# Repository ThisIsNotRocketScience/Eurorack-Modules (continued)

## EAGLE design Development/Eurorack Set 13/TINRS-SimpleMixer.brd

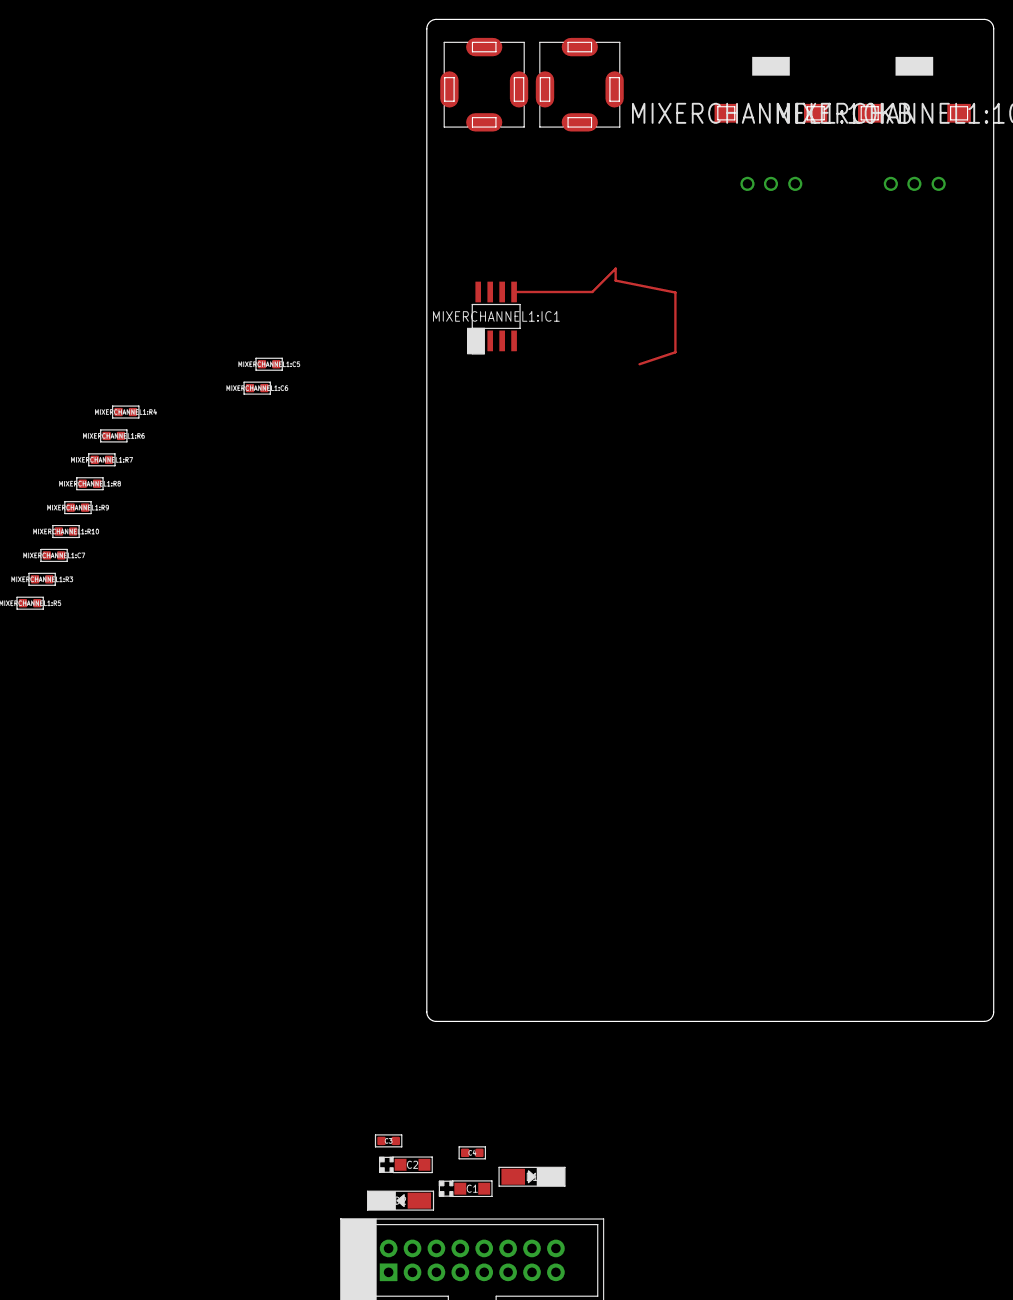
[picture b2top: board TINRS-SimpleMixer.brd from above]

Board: 2 copper layers, 60.2 x 106.5 mm, 24 parts (0 on the bottom side), 16 nets.

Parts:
C1, C2: CASE-A_3216
C3, C4: 100n; C0603
D1, D2: DO-214AC
J1: POWERSHROUDED; POWER_16_SHROUDED
MIXERCHANNEL1:10KA, MIXERCHANNEL1:10KB: ALPS_POT_SQUAREHOLES
MIXERCHANNEL1:C5, MIXERCHANNEL1:C6: 100n; C0603
MIXERCHANNEL1:C7: 100p; C0603
MIXERCHANNEL1:IC1: NE5532D; SO08
MIXERCHANNEL1:J2, MIXERCHANNEL1:J3: JACK; 3.5MM-JACK-SWITCH-13MM-NOHOLES
MIXERCHANNEL1:R3, MIXERCHANNEL1:R5: 2.2k; R0603
MIXERCHANNEL1:R4, MIXERCHANNEL1:R6, MIXERCHANNEL1:R7, MIXERCHANNEL1:R8, MIXERCHANNEL1:R9: 4.7k; R0603
MIXERCHANNEL1:R10: 56; R0603
PCB1: EURORACK_PCB12HP; EURORACK12HPPCB

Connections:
12V: C1.+, C4.1, D1.2, MIXERCHANNEL1:C6.1, MIXERCHANNEL1:IC1.8
-12V: C2.-, C3.2, D2.1, MIXERCHANNEL1:C5.2, MIXERCHANNEL1:IC1.4
GND: C1.-, C2.+, C3.1, C4.2, J1.3, J1.4, J1.5, J1.6, J1.7, J1.8, MIXERCHANNEL1:10KA.P$1, MIXERCHANNEL1:10KB.P$2, MIXERCHANNEL1:C5.1, MIXERCHANNEL1:C6.2, MIXERCHANNEL1:IC1.3, MIXERCHANNEL1:IC1.5, MIXERCHANNEL1:J2.RING_B@1, MIXERCHANNEL1:J2.RING_T@3, MIXERCHANNEL1:J2.SWITCH_B@1, MIXERCHANNEL1:J2.SWITCH_T@3, MIXERCHANNEL1:J3.RING_B@1, MIXERCHANNEL1:J3.RING_T@3, MIXERCHANNEL1:J3.SWITCH_B@1, MIXERCHANNEL1:J3.SWITCH_T@3
MIXERCHANNEL1:N$1: MIXERCHANNEL1:C7.2, MIXERCHANNEL1:IC1.6, MIXERCHANNEL1:R6.2, MIXERCHANNEL1:R7.1
MIXERCHANNEL1:N$2: MIXERCHANNEL1:IC1.2, MIXERCHANNEL1:R4.2, MIXERCHANNEL1:R8.2, MIXERCHANNEL1:R9.1
MIXERCHANNEL1:N$3: MIXERCHANNEL1:10KA.P$2, MIXERCHANNEL1:R6.1
MIXERCHANNEL1:N$4: MIXERCHANNEL1:10KA.P$3, MIXERCHANNEL1:IC1.1, MIXERCHANNEL1:R9.2
MIXERCHANNEL1:N$5: MIXERCHANNEL1:R3.1, MIXERCHANNEL1:R5.1, MIXERCHANNEL1:R7.2, MIXERCHANNEL1:R10.2
MIXERCHANNEL1:N$10: MIXERCHANNEL1:J2.TIP_B@1, MIXERCHANNEL1:J2.TIP_T@3, MIXERCHANNEL1:R4.1
MIXERCHANNEL1:N$11: MIXERCHANNEL1:J3.TIP_B@1, MIXERCHANNEL1:J3.TIP_T@3, MIXERCHANNEL1:R8.1
MIXERCHANNEL1:N$12: MIXERCHANNEL1:IC1.7, MIXERCHANNEL1:R10.1
MIXERCHANNEL1:N$13: MIXERCHANNEL1:C7.1, MIXERCHANNEL1:IC1.7
MIXERCHANNEL1:OUT_L: MIXERCHANNEL1:10KB.P$3, MIXERCHANNEL1:R5.2
MIXERCHANNEL1:OUT_R: MIXERCHANNEL1:10KB.P$1, MIXERCHANNEL1:R3.2
unnamed: D1.1, J1.9, J1.10
unnamed: D2.2, J1.1, J1.2

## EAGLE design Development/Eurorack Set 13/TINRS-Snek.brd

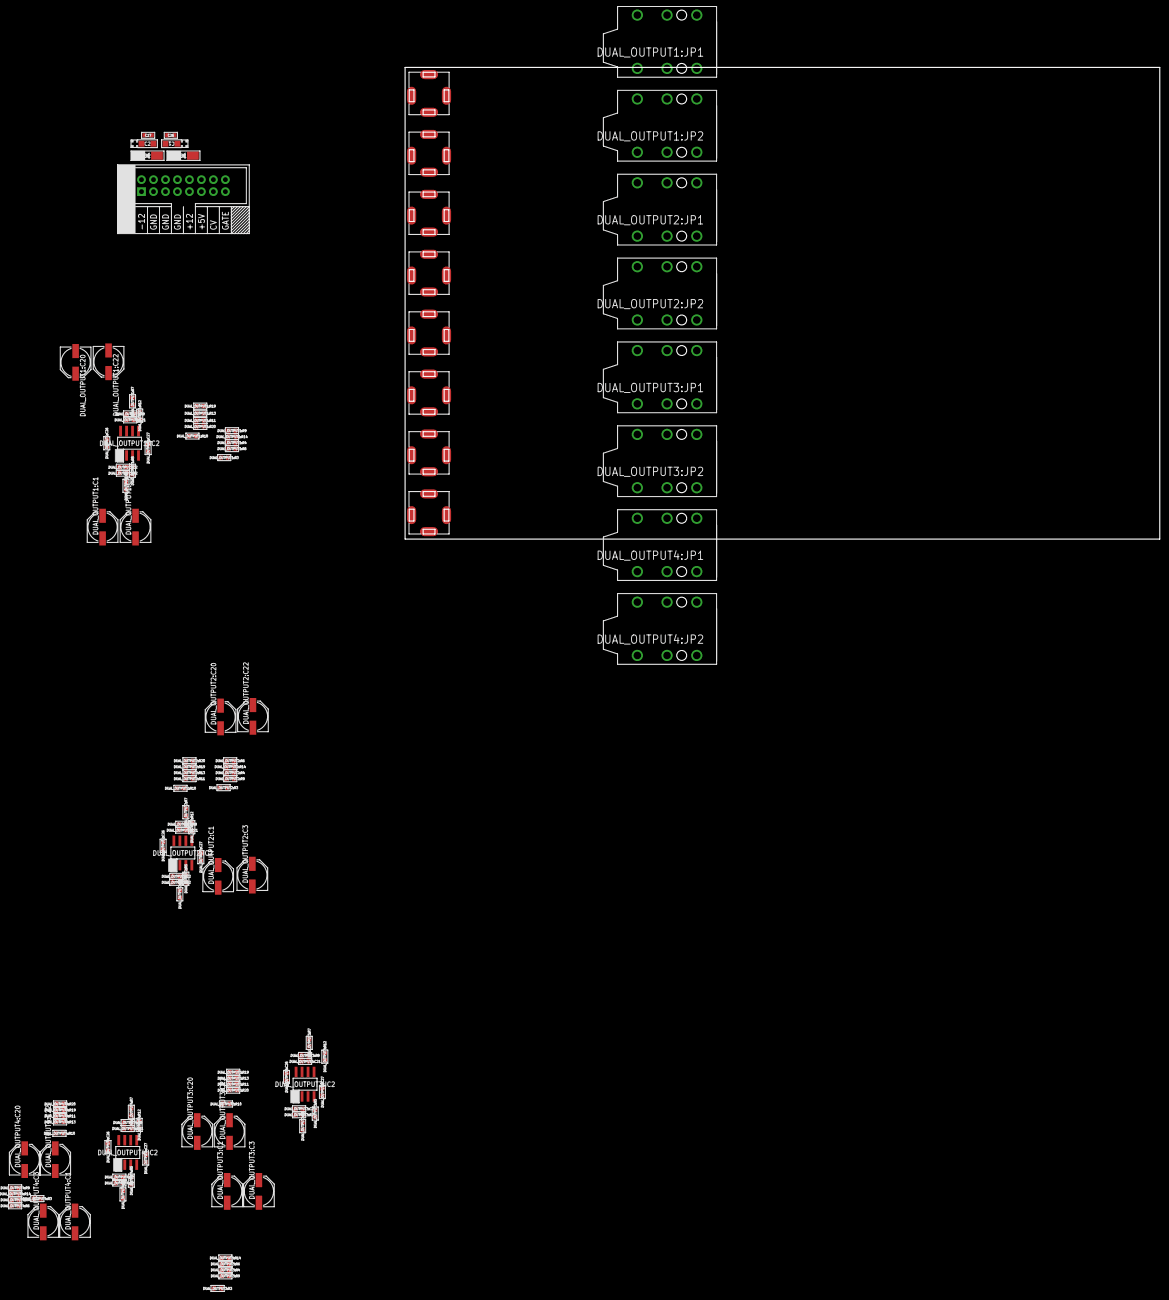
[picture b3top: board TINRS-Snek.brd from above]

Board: 2 copper layers, 160.0 x 100.0 mm, 123 parts (0 on the bottom side), 64 nets, no tracks yet.

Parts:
C1, C2: 10u; CASE-A_3216
C26, C27: 100n; C0603
D1, D2: DO-214AC
DUAL_OUTPUT1:C1, DUAL_OUTPUT1:C3, DUAL_OUTPUT1:C20, DUAL_OUTPUT1:C22, DUAL_OUTPUT2:C1, DUAL_OUTPUT2:C3, DUAL_OUTPUT2:C20, DUAL_OUTPUT2:C22, DUAL_OUTPUT3:C1, DUAL_OUTPUT3:C3, DUAL_OUTPUT3:C20, DUAL_OUTPUT3:C22, DUAL_OUTPUT4:C1, DUAL_OUTPUT4:C3, DUAL_OUTPUT4:C20, DUAL_OUTPUT4:C22: 100u; PANASONIC_D
DUAL_OUTPUT1:C2, DUAL_OUTPUT1:C21, DUAL_OUTPUT2:C2, DUAL_OUTPUT2:C21, DUAL_OUTPUT3:C2, DUAL_OUTPUT3:C21, DUAL_OUTPUT4:C2, DUAL_OUTPUT4:C21: 22p; C0603
DUAL_OUTPUT1:C26, DUAL_OUTPUT1:C27, DUAL_OUTPUT2:C26, DUAL_OUTPUT2:C27, DUAL_OUTPUT3:C26, DUAL_OUTPUT3:C27, DUAL_OUTPUT4:C26, DUAL_OUTPUT4:C27: 100n; C0603
DUAL_OUTPUT1:IC2, DUAL_OUTPUT2:IC2, DUAL_OUTPUT3:IC2, DUAL_OUTPUT4:IC2: NE5532D; SO08
DUAL_OUTPUT1:J1, DUAL_OUTPUT1:J2, DUAL_OUTPUT2:J1, DUAL_OUTPUT2:J2, DUAL_OUTPUT3:J1, DUAL_OUTPUT3:J2, DUAL_OUTPUT4:J1, DUAL_OUTPUT4:J2: JACK; 3.5MM-JACK-SWITCH-13MM-NOHOLES
DUAL_OUTPUT1:JP1, DUAL_OUTPUT1:JP2, DUAL_OUTPUT2:JP1, DUAL_OUTPUT2:JP2, DUAL_OUTPUT3:JP1, DUAL_OUTPUT3:JP2, DUAL_OUTPUT4:JP1, DUAL_OUTPUT4:JP2: AUDIO-JACK-.25-INCH-HORIZ-PTH
DUAL_OUTPUT1:R1, DUAL_OUTPUT1:R2, DUAL_OUTPUT1:R7, DUAL_OUTPUT1:R8, DUAL_OUTPUT2:R1, DUAL_OUTPUT2:R2, DUAL_OUTPUT2:R7, DUAL_OUTPUT2:R8, DUAL_OUTPUT3:R1, DUAL_OUTPUT3:R2, DUAL_OUTPUT3:R7, DUAL_OUTPUT3:R8, DUAL_OUTPUT4:R1, DUAL_OUTPUT4:R2, DUAL_OUTPUT4:R7, DUAL_OUTPUT4:R8: 4.7k; R0603
DUAL_OUTPUT1:R3, DUAL_OUTPUT1:R10, DUAL_OUTPUT2:R3, DUAL_OUTPUT2:R10, DUAL_OUTPUT3:R3, DUAL_OUTPUT3:R10, DUAL_OUTPUT4:R3, DUAL_OUTPUT4:R10: 56k; R0603
DUAL_OUTPUT1:R4, DUAL_OUTPUT1:R6, DUAL_OUTPUT1:R9, DUAL_OUTPUT1:R11, DUAL_OUTPUT1:R13, DUAL_OUTPUT1:R14, DUAL_OUTPUT1:R19, DUAL_OUTPUT1:R20, DUAL_OUTPUT2:R4, DUAL_OUTPUT2:R6, DUAL_OUTPUT2:R9, DUAL_OUTPUT2:R11, DUAL_OUTPUT2:R13, DUAL_OUTPUT2:R14, DUAL_OUTPUT2:R19, DUAL_OUTPUT2:R20, DUAL_OUTPUT3:R4, DUAL_OUTPUT3:R6, DUAL_OUTPUT3:R9, DUAL_OUTPUT3:R11, DUAL_OUTPUT3:R13, DUAL_OUTPUT3:R14, DUAL_OUTPUT3:R19, DUAL_OUTPUT3:R20, DUAL_OUTPUT4:R4, DUAL_OUTPUT4:R6, DUAL_OUTPUT4:R9, DUAL_OUTPUT4:R11, DUAL_OUTPUT4:R13, DUAL_OUTPUT4:R14, DUAL_OUTPUT4:R19, DUAL_OUTPUT4:R20: 220; R0603
DUAL_OUTPUT1:R5, DUAL_OUTPUT1:R12, DUAL_OUTPUT2:R5, DUAL_OUTPUT2:R12, DUAL_OUTPUT3:R5, DUAL_OUTPUT3:R12, DUAL_OUTPUT4:R5, DUAL_OUTPUT4:R12: 27; R0603
J5: POWERSHROUDED; POWER_16_SHROUDED

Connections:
5V: J5.11, J5.12
12V: C1.+, C26.2, D1.2, DUAL_OUTPUT1:C26.2, DUAL_OUTPUT1:IC2.8, DUAL_OUTPUT2:C26.2, DUAL_OUTPUT2:IC2.8, DUAL_OUTPUT3:C26.2, DUAL_OUTPUT3:IC2.8, DUAL_OUTPUT4:C26.2, DUAL_OUTPUT4:IC2.8
-12V: C2.-, C27.1, D2.1, DUAL_OUTPUT1:C27.1, DUAL_OUTPUT1:IC2.4, DUAL_OUTPUT2:C27.1, DUAL_OUTPUT2:IC2.4, DUAL_OUTPUT3:C27.1, DUAL_OUTPUT3:IC2.4, DUAL_OUTPUT4:C27.1, DUAL_OUTPUT4:IC2.4
CV1: J5.13, J5.14
DUAL_OUTPUT1:N$1: DUAL_OUTPUT1:C21.1, DUAL_OUTPUT1:IC2.6, DUAL_OUTPUT1:R7.1, DUAL_OUTPUT1:R8.2
DUAL_OUTPUT1:N$2: DUAL_OUTPUT1:C20.+, DUAL_OUTPUT1:C21.2, DUAL_OUTPUT1:IC2.7, DUAL_OUTPUT1:R8.1
DUAL_OUTPUT1:N$3: DUAL_OUTPUT1:C22.+, DUAL_OUTPUT1:R10.1, DUAL_OUTPUT1:R11.1, DUAL_OUTPUT1:R13.1, DUAL_OUTPUT1:R19.1, DUAL_OUTPUT1:R20.1
DUAL_OUTPUT1:N$4: DUAL_OUTPUT1:IC2.5, DUAL_OUTPUT1:R12.1
DUAL_OUTPUT1:N$5: DUAL_OUTPUT1:C2.1, DUAL_OUTPUT1:IC2.2, DUAL_OUTPUT1:R1.1, DUAL_OUTPUT1:R2.2
DUAL_OUTPUT1:N$6: DUAL_OUTPUT1:C1.+, DUAL_OUTPUT1:C2.2, DUAL_OUTPUT1:IC2.1, DUAL_OUTPUT1:R2.1
DUAL_OUTPUT1:N$7: DUAL_OUTPUT1:C3.+, DUAL_OUTPUT1:R3.1, DUAL_OUTPUT1:R4.1, DUAL_OUTPUT1:R6.1, DUAL_OUTPUT1:R9.1, DUAL_OUTPUT1:R14.1
DUAL_OUTPUT1:N$8: DUAL_OUTPUT1:IC2.3, DUAL_OUTPUT1:R5.1
DUAL_OUTPUT1:N$11: DUAL_OUTPUT1:C20.-, DUAL_OUTPUT1:C22.-
DUAL_OUTPUT1:N$12: DUAL_OUTPUT1:C1.-, DUAL_OUTPUT1:C3.-
DUAL_OUTPUT1:OUT1: DUAL_OUTPUT1:J1.TIP_B@1, DUAL_OUTPUT1:J1.TIP_T@3, DUAL_OUTPUT1:R1.2
DUAL_OUTPUT1:OUT2: DUAL_OUTPUT1:J2.TIP_B@1, DUAL_OUTPUT1:J2.TIP_T@3, DUAL_OUTPUT1:R7.2
DUAL_OUTPUT1:TIP1: DUAL_OUTPUT1:JP1.P$6, DUAL_OUTPUT1:R4.2, DUAL_OUTPUT1:R6.2, DUAL_OUTPUT1:R9.2, DUAL_OUTPUT1:R14.2
DUAL_OUTPUT1:TIP2: DUAL_OUTPUT1:JP2.P$6, DUAL_OUTPUT1:R11.2, DUAL_OUTPUT1:R13.2, DUAL_OUTPUT1:R19.2, DUAL_OUTPUT1:R20.2
DUAL_OUTPUT2:N$1: DUAL_OUTPUT2:C21.1, DUAL_OUTPUT2:IC2.6, DUAL_OUTPUT2:R7.1, DUAL_OUTPUT2:R8.2
DUAL_OUTPUT2:N$2: DUAL_OUTPUT2:C20.+, DUAL_OUTPUT2:C21.2, DUAL_OUTPUT2:IC2.7, DUAL_OUTPUT2:R8.1
DUAL_OUTPUT2:N$3: DUAL_OUTPUT2:C22.+, DUAL_OUTPUT2:R10.1, DUAL_OUTPUT2:R11.1, DUAL_OUTPUT2:R13.1, DUAL_OUTPUT2:R19.1, DUAL_OUTPUT2:R20.1
DUAL_OUTPUT2:N$4: DUAL_OUTPUT2:IC2.5, DUAL_OUTPUT2:R12.1
DUAL_OUTPUT2:N$5: DUAL_OUTPUT2:C2.1, DUAL_OUTPUT2:IC2.2, DUAL_OUTPUT2:R1.1, DUAL_OUTPUT2:R2.2
DUAL_OUTPUT2:N$6: DUAL_OUTPUT2:C1.+, DUAL_OUTPUT2:C2.2, DUAL_OUTPUT2:IC2.1, DUAL_OUTPUT2:R2.1
DUAL_OUTPUT2:N$7: DUAL_OUTPUT2:C3.+, DUAL_OUTPUT2:R3.1, DUAL_OUTPUT2:R4.1, DUAL_OUTPUT2:R6.1, DUAL_OUTPUT2:R9.1, DUAL_OUTPUT2:R14.1
DUAL_OUTPUT2:N$8: DUAL_OUTPUT2:IC2.3, DUAL_OUTPUT2:R5.1
DUAL_OUTPUT2:N$11: DUAL_OUTPUT2:C20.-, DUAL_OUTPUT2:C22.-
DUAL_OUTPUT2:N$12: DUAL_OUTPUT2:C1.-, DUAL_OUTPUT2:C3.-
DUAL_OUTPUT2:OUT1: DUAL_OUTPUT2:J1.TIP_B@1, DUAL_OUTPUT2:J1.TIP_T@3, DUAL_OUTPUT2:R1.2
DUAL_OUTPUT2:OUT2: DUAL_OUTPUT2:J2.TIP_B@1, DUAL_OUTPUT2:J2.TIP_T@3, DUAL_OUTPUT2:R7.2
DUAL_OUTPUT2:TIP1: DUAL_OUTPUT2:JP1.P$6, DUAL_OUTPUT2:R4.2, DUAL_OUTPUT2:R6.2, DUAL_OUTPUT2:R9.2, DUAL_OUTPUT2:R14.2
DUAL_OUTPUT2:TIP2: DUAL_OUTPUT2:JP2.P$6, DUAL_OUTPUT2:R11.2, DUAL_OUTPUT2:R13.2, DUAL_OUTPUT2:R19.2, DUAL_OUTPUT2:R20.2
DUAL_OUTPUT3:N$1: DUAL_OUTPUT3:C21.1, DUAL_OUTPUT3:IC2.6, DUAL_OUTPUT3:R7.1, DUAL_OUTPUT3:R8.2
DUAL_OUTPUT3:N$2: DUAL_OUTPUT3:C20.+, DUAL_OUTPUT3:C21.2, DUAL_OUTPUT3:IC2.7, DUAL_OUTPUT3:R8.1
DUAL_OUTPUT3:N$3: DUAL_OUTPUT3:C22.+, DUAL_OUTPUT3:R10.1, DUAL_OUTPUT3:R11.1, DUAL_OUTPUT3:R13.1, DUAL_OUTPUT3:R19.1, DUAL_OUTPUT3:R20.1
DUAL_OUTPUT3:N$4: DUAL_OUTPUT3:IC2.5, DUAL_OUTPUT3:R12.1
DUAL_OUTPUT3:N$5: DUAL_OUTPUT3:C2.1, DUAL_OUTPUT3:IC2.2, DUAL_OUTPUT3:R1.1, DUAL_OUTPUT3:R2.2
DUAL_OUTPUT3:N$6: DUAL_OUTPUT3:C1.+, DUAL_OUTPUT3:C2.2, DUAL_OUTPUT3:IC2.1, DUAL_OUTPUT3:R2.1
DUAL_OUTPUT3:N$7: DUAL_OUTPUT3:C3.+, DUAL_OUTPUT3:R3.1, DUAL_OUTPUT3:R4.1, DUAL_OUTPUT3:R6.1, DUAL_OUTPUT3:R9.1, DUAL_OUTPUT3:R14.1
DUAL_OUTPUT3:N$8: DUAL_OUTPUT3:IC2.3, DUAL_OUTPUT3:R5.1
DUAL_OUTPUT3:N$11: DUAL_OUTPUT3:C20.-, DUAL_OUTPUT3:C22.-
DUAL_OUTPUT3:N$12: DUAL_OUTPUT3:C1.-, DUAL_OUTPUT3:C3.-
DUAL_OUTPUT3:OUT1: DUAL_OUTPUT3:J1.TIP_B@1, DUAL_OUTPUT3:J1.TIP_T@3, DUAL_OUTPUT3:R1.2
DUAL_OUTPUT3:OUT2: DUAL_OUTPUT3:J2.TIP_B@1, DUAL_OUTPUT3:J2.TIP_T@3, DUAL_OUTPUT3:R7.2
DUAL_OUTPUT3:TIP1: DUAL_OUTPUT3:JP1.P$6, DUAL_OUTPUT3:R4.2, DUAL_OUTPUT3:R6.2, DUAL_OUTPUT3:R9.2, DUAL_OUTPUT3:R14.2
DUAL_OUTPUT3:TIP2: DUAL_OUTPUT3:JP2.P$6, DUAL_OUTPUT3:R11.2, DUAL_OUTPUT3:R13.2, DUAL_OUTPUT3:R19.2, DUAL_OUTPUT3:R20.2
DUAL_OUTPUT4:N$1: DUAL_OUTPUT4:C21.1, DUAL_OUTPUT4:IC2.6, DUAL_OUTPUT4:R7.1, DUAL_OUTPUT4:R8.2
DUAL_OUTPUT4:N$2: DUAL_OUTPUT4:C20.+, DUAL_OUTPUT4:C21.2, DUAL_OUTPUT4:IC2.7, DUAL_OUTPUT4:R8.1
DUAL_OUTPUT4:N$3: DUAL_OUTPUT4:C22.+, DUAL_OUTPUT4:R10.1, DUAL_OUTPUT4:R11.1, DUAL_OUTPUT4:R13.1, DUAL_OUTPUT4:R19.1, DUAL_OUTPUT4:R20.1
DUAL_OUTPUT4:N$4: DUAL_OUTPUT4:IC2.5, DUAL_OUTPUT4:R12.1
DUAL_OUTPUT4:N$5: DUAL_OUTPUT4:C2.1, DUAL_OUTPUT4:IC2.2, DUAL_OUTPUT4:R1.1, DUAL_OUTPUT4:R2.2
DUAL_OUTPUT4:N$6: DUAL_OUTPUT4:C1.+, DUAL_OUTPUT4:C2.2, DUAL_OUTPUT4:IC2.1, DUAL_OUTPUT4:R2.1
DUAL_OUTPUT4:N$7: DUAL_OUTPUT4:C3.+, DUAL_OUTPUT4:R3.1, DUAL_OUTPUT4:R4.1, DUAL_OUTPUT4:R6.1, DUAL_OUTPUT4:R9.1, DUAL_OUTPUT4:R14.1
DUAL_OUTPUT4:N$8: DUAL_OUTPUT4:IC2.3, DUAL_OUTPUT4:R5.1
DUAL_OUTPUT4:N$11: DUAL_OUTPUT4:C20.-, DUAL_OUTPUT4:C22.-
DUAL_OUTPUT4:N$12: DUAL_OUTPUT4:C1.-, DUAL_OUTPUT4:C3.-
DUAL_OUTPUT4:OUT1: DUAL_OUTPUT4:J1.TIP_B@1, DUAL_OUTPUT4:J1.TIP_T@3, DUAL_OUTPUT4:R1.2
DUAL_OUTPUT4:OUT2: DUAL_OUTPUT4:J2.TIP_B@1, DUAL_OUTPUT4:J2.TIP_T@3, DUAL_OUTPUT4:R7.2
DUAL_OUTPUT4:TIP1: DUAL_OUTPUT4:JP1.P$6, DUAL_OUTPUT4:R4.2, DUAL_OUTPUT4:R6.2, DUAL_OUTPUT4:R9.2, DUAL_OUTPUT4:R14.2
DUAL_OUTPUT4:TIP2: DUAL_OUTPUT4:JP2.P$6, DUAL_OUTPUT4:R11.2, DUAL_OUTPUT4:R13.2, DUAL_OUTPUT4:R19.2, DUAL_OUTPUT4:R20.2
G1: J5.15, J5.16
GND: C1.-, C2.+, C26.1, DUAL_OUTPUT1:C26.1, DUAL_OUTPUT1:C27.2, DUAL_OUTPUT1:J1.RING_B@1, DUAL_OUTPUT1:J1.RING_T@3, DUAL_OUTPUT1:J1.SWITCH_B@1, DUAL_OUTPUT1:J1.SWITCH_T@3, DUAL_OUTPUT1:J2.RING_B@1, DUAL_OUTPUT1:J2.RING_T@3, DUAL_OUTPUT1:J2.SWITCH_B@1, DUAL_OUTPUT1:J2.SWITCH_T@3, DUAL_OUTPUT1:JP1.P$2, DUAL_OUTPUT1:JP1.P$3, DUAL_OUTPUT1:JP1.P$4, DUAL_OUTPUT1:JP2.P$2, DUAL_OUTPUT1:JP2.P$3, DUAL_OUTPUT1:JP2.P$4, DUAL_OUTPUT1:R3.2, DUAL_OUTPUT1:R5.2, DUAL_OUTPUT1:R10.2, DUAL_OUTPUT1:R12.2, DUAL_OUTPUT2:C26.1, DUAL_OUTPUT2:C27.2, DUAL_OUTPUT2:J1.RING_B@1, DUAL_OUTPUT2:J1.RING_T@3, DUAL_OUTPUT2:J1.SWITCH_B@1, DUAL_OUTPUT2:J1.SWITCH_T@3, DUAL_OUTPUT2:J2.RING_B@1, DUAL_OUTPUT2:J2.RING_T@3, DUAL_OUTPUT2:J2.SWITCH_B@1, DUAL_OUTPUT2:J2.SWITCH_T@3, DUAL_OUTPUT2:JP1.P$2, DUAL_OUTPUT2:JP1.P$3, DUAL_OUTPUT2:JP1.P$4, DUAL_OUTPUT2:JP2.P$2, DUAL_OUTPUT2:JP2.P$3, DUAL_OUTPUT2:JP2.P$4, DUAL_OUTPUT2:R3.2, DUAL_OUTPUT2:R5.2, DUAL_OUTPUT2:R10.2, DUAL_OUTPUT2:R12.2, DUAL_OUTPUT3:C26.1, DUAL_OUTPUT3:C27.2, DUAL_OUTPUT3:J1.RING_B@1, DUAL_OUTPUT3:J1.RING_T@3, DUAL_OUTPUT3:J1.SWITCH_B@1, DUAL_OUTPUT3:J1.SWITCH_T@3, DUAL_OUTPUT3:J2.RING_B@1, DUAL_OUTPUT3:J2.RING_T@3, DUAL_OUTPUT3:J2.SWITCH_B@1, DUAL_OUTPUT3:J2.SWITCH_T@3, DUAL_OUTPUT3:JP1.P$2, DUAL_OUTPUT3:JP1.P$3, DUAL_OUTPUT3:JP1.P$4, DUAL_OUTPUT3:JP2.P$2, DUAL_OUTPUT3:JP2.P$3, DUAL_OUTPUT3:JP2.P$4, DUAL_OUTPUT3:R3.2, DUAL_OUTPUT3:R5.2, DUAL_OUTPUT3:R10.2, DUAL_OUTPUT3:R12.2, DUAL_OUTPUT4:C26.1, DUAL_OUTPUT4:C27.2, DUAL_OUTPUT4:J1.RING_B@1, DUAL_OUTPUT4:J1.RING_T@3, DUAL_OUTPUT4:J1.SWITCH_B@1, DUAL_OUTPUT4:J1.SWITCH_T@3, DUAL_OUTPUT4:J2.RING_B@1, DUAL_OUTPUT4:J2.RING_T@3, DUAL_OUTPUT4:J2.SWITCH_B@1, DUAL_OUTPUT4:J2.SWITCH_T@3, DUAL_OUTPUT4:JP1.P$2, DUAL_OUTPUT4:JP1.P$3, DUAL_OUTPUT4:JP1.P$4, DUAL_OUTPUT4:JP2.P$2, DUAL_OUTPUT4:JP2.P$3, DUAL_OUTPUT4:JP2.P$4, DUAL_OUTPUT4:R3.2, DUAL_OUTPUT4:R5.2, DUAL_OUTPUT4:R10.2, DUAL_OUTPUT4:R12.2, J5.3, J5.4, J5.5, J5.6, J5.7, J5.8
unnamed: D1.1, J5.9, J5.10
unnamed: D2.2, J5.1, J5.2
